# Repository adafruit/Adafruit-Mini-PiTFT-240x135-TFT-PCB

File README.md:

## Adafruit Mini PiTFT - 135x240 and 240x240 Color TFT Add-ons for Raspberry Pi PCB

<a href="http://www.adafruit.com/products/4393"><br/>
<a href="http://www.adafruit.com/products/4484"><br/>
Click here to purchase one from the Adafruit shop</a>

PCB files for the Adafruit Mini PiTFT - 135x240 and 240x240 Color TFT Add-ons for Raspberry Pi. 

Format is EagleCAD schematic and board layout
* https://www.adafruit.com/product/4393
* https://www.adafruit.com/product/4484

### Description

If you're looking for the most compact li'l color display for a [Raspberry Pi](https://www.adafruit.com/category/361) (most likely a [Pi Zero](https://www.adafruit.com/category/813)) project, this might be just the thing you need!

The **Adafruit Mini PiTFT - 135x240 Color TFT Add-on for Raspberry Pi** and the **Adafruit Mini PiTFT - 1.3" 240x240 Color TFT Add-on for Raspberry Pi** are your little TFT pals, ready to snap onto any and all Raspberry Pi computers, to give you a little display. The Mini PiTFT comes with a full color 240x135 or 240x240 pixel IPS display with great visibility at all angles. The TFT uses only the SPI port so its very fast, and we leave plenty of pins remaining available for buttons, LEDs, sensors, etc. It's also nice and compact so it will fit into any case.

This display is super small, only about 1.14" diagonal or 1.3" diagonal, but since it is an IPS display, its very readable with high contrast and visibility. We had a little space on the top so we give you two tactile buttons on GPIO pins so you can create a simple user interface. [On the bottom we have a Qwiic/STEMMA QT connector for I2C sensors and device so you can plug and play any of our STEMMA QT devices](https://www.adafruit.com/?q=stemma%20qt).

Using the display is very easy, we have a kernel driver and Python library for the ST7789 chipset. You can set it up as a console output so you can have text and user interface through the Raspberry Pi OS or you draw images, text, whatever you like, using the Python imaging library. Our tests showed ~15 FPS update rates so you can do animations or simple video.

**Comes completely pre-assembled and tested** so you don't need to do anything but plug it in and install our Python code! **Works with any Raspberry Pi computer.**

### License

Adafruit invests time and resources providing this open source design, please support Adafruit and open-source hardware by purchasing products from [Adafruit](https://www.adafruit.com)!

Designed by Limor Fried/Ladyada for Adafruit Industries.

Creative Commons Attribution/Share-Alike, all text above must be included in any redistribution. 
See license.txt for additional details.

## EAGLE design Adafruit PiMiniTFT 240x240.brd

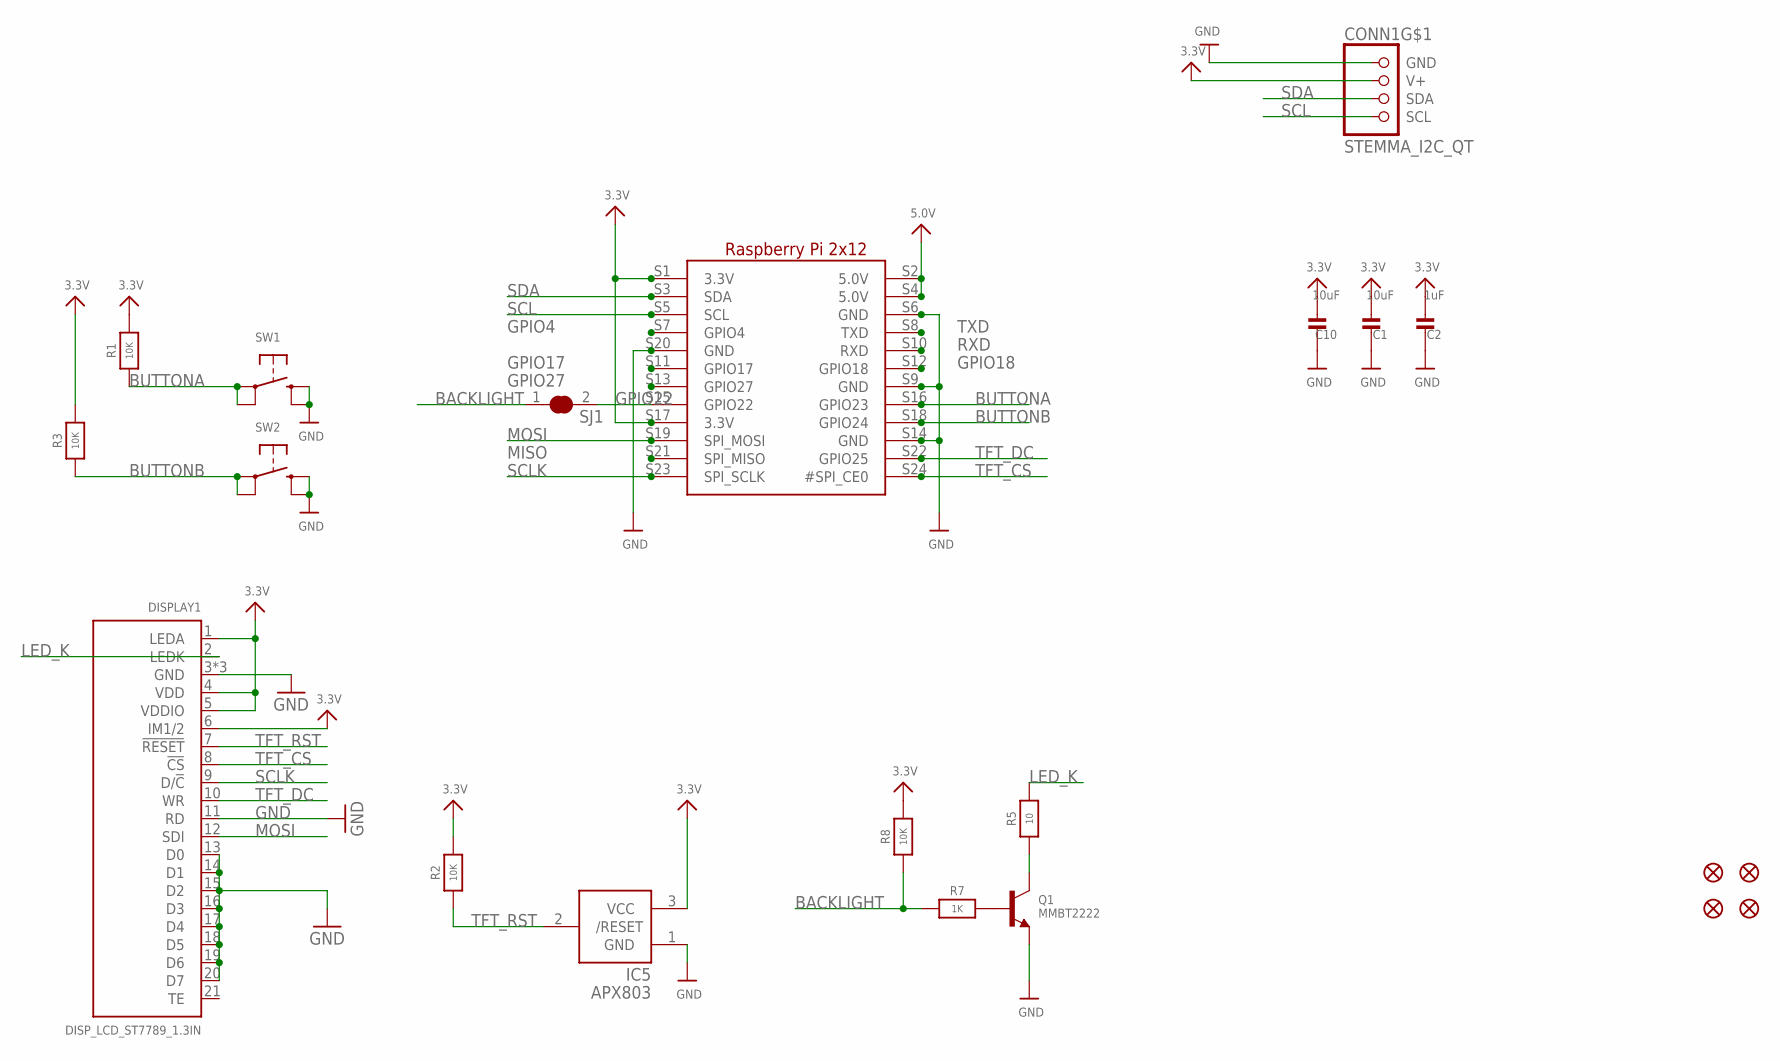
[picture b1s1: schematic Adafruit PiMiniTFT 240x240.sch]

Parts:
C1, C10: 10uF; 0805-NO
C2: 1uF; 0603-NO
CONN1: STEMMA_I2C_QT; JST_SH4
DISPLAY1: DISP_LCD_ST7789_1.3IN; TFT_1.3IN_240X240_24P
FID1, FID2, FID3, FID4: FIDUCIAL_1MM
IC5: APX803; SOT23
Q1: MMBT2222; SOT23-WIDE
R1, R2, R3, R8: 10K; 0603-NO
R5: 10; 0603-NO
R7: 1K; 0603-NO
RASPI1: RASPBERRYPI_2X12_SMT
SJ1: SOLDERJUMPER_CLOSED; SOLDERJUMPER_CLOSEDWIRE
SW1, SW2: SWITCH_TACT_SMT_EVQQ2_SMALL; EVQ-Q2_SMALLER

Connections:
3.3V: C1.2, C2.2, C10.2, CONN1.2 (V+), DISPLAY1.1 (LEDA), DISPLAY1.4 (VDD), DISPLAY1.5 (VDDIO), DISPLAY1.6 (IM1/2), IC5.3 (VCC), R1.2, R2.2, R3.2, R8.2, RASPI1.S1 (3.3V), RASPI1.S17 (3.3V)
5.0V: RASPI1.S2 (5.0V), RASPI1.S4 (5.0V)
BACKLIGHT: R7.1, R8.1, SJ1.1
BUTTONA: R1.1, RASPI1.S16 (GPIO23), SW1.A, SW1.A' (P1)
BUTTONB: R3.1, RASPI1.S18 (GPIO24), SW2.A, SW2.A' (P1)
GND: C1.1, C2.1, C10.1, CONN1.1 (GND), DISPLAY1.3 (GND), DISPLAY1.11 (RD), DISPLAY1.13 (D0), DISPLAY1.14 (D1), DISPLAY1.15 (D2), DISPLAY1.16 (D3), DISPLAY1.17 (D4), DISPLAY1.18 (D5), DISPLAY1.19 (D6), DISPLAY1.20 (D7), DISPLAY1.23 (GND), DISPLAY1.24 (GND), IC5.1 (GND), Q1.2 (E), RASPI1.S6 (GND), RASPI1.S9 (GND), RASPI1.S14 (GND), RASPI1.S20 (GND), SW1.B (S), SW1.B' (S1), SW2.B (S), SW2.B' (S1)
GPIO4: RASPI1.S7 (GPIO4)
GPIO17: RASPI1.S11 (GPIO17)
GPIO18: RASPI1.S12 (GPIO18)
GPIO22: RASPI1.S15 (GPIO22), SJ1.2
GPIO27: RASPI1.S13 (GPIO27)
LED_K: DISPLAY1.2 (LEDK), R5.2
MISO: RASPI1.S21 (SPI_MISO)
MOSI: DISPLAY1.12 (SDI), RASPI1.S19 (SPI_MOSI)
unnamed: Q1.1 (B), R7.2
unnamed: Q1.3 (C), R5.1
RXD: RASPI1.S10 (RXD)
SCL: CONN1.4 (SCL), RASPI1.S5 (SCL)
SCLK: DISPLAY1.9 (D/!C), RASPI1.S23 (SPI_SCLK)
SDA: CONN1.3 (SDA), RASPI1.S3 (SDA)
TFT_CS: DISPLAY1.8 (!CS), RASPI1.S24 (#SPI_CE0)
TFT_DC: DISPLAY1.10 (WR), RASPI1.S22 (GPIO25)
TFT_RST: DISPLAY1.7 (!RESET), IC5.2 (/RESET), R2.1
TXD: RASPI1.S8 (TXD)

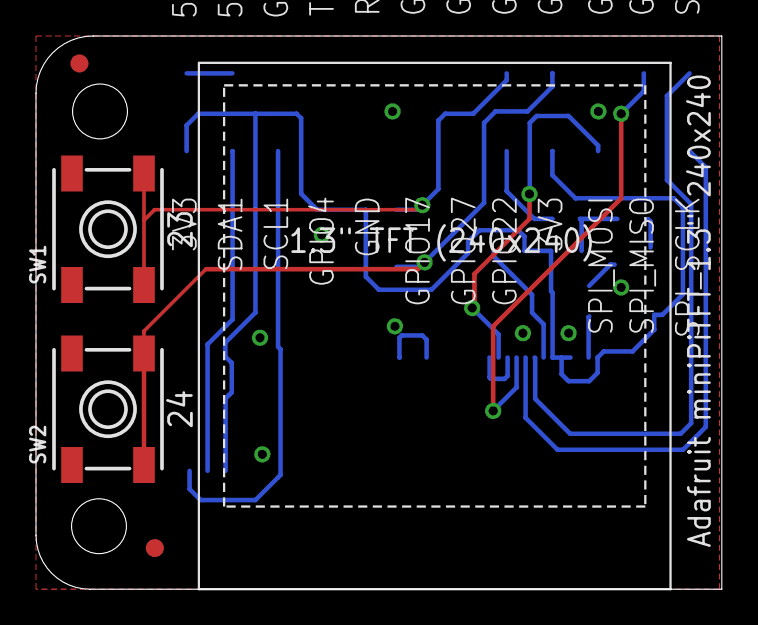
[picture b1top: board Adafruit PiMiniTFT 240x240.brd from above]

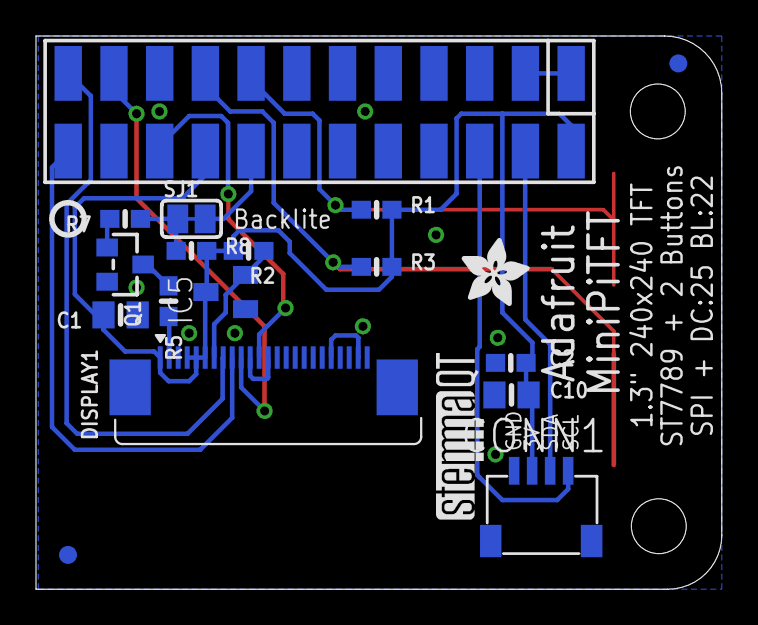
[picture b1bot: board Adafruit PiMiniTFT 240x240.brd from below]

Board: 2 copper layers, 38.1 x 30.7 mm, 24 parts (19 on the bottom side), 17 nets.

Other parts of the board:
U$4: MICROSD; ADAFRUIT_3.5MM
U$6: PCBFEAT-REV-040
U$15: STEMMAQT

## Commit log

2020-10-26 Add asset
2020-10-26 Adding board files.
2020-10-26 Update README.
